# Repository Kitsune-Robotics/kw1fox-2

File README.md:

# kw1fox-2
Software and tools for the KW1FOX-2 radio station

## To clone

```
git clone --recurse-submodules https://github.com/Kitsune-Robotics/kw1fox-2
```

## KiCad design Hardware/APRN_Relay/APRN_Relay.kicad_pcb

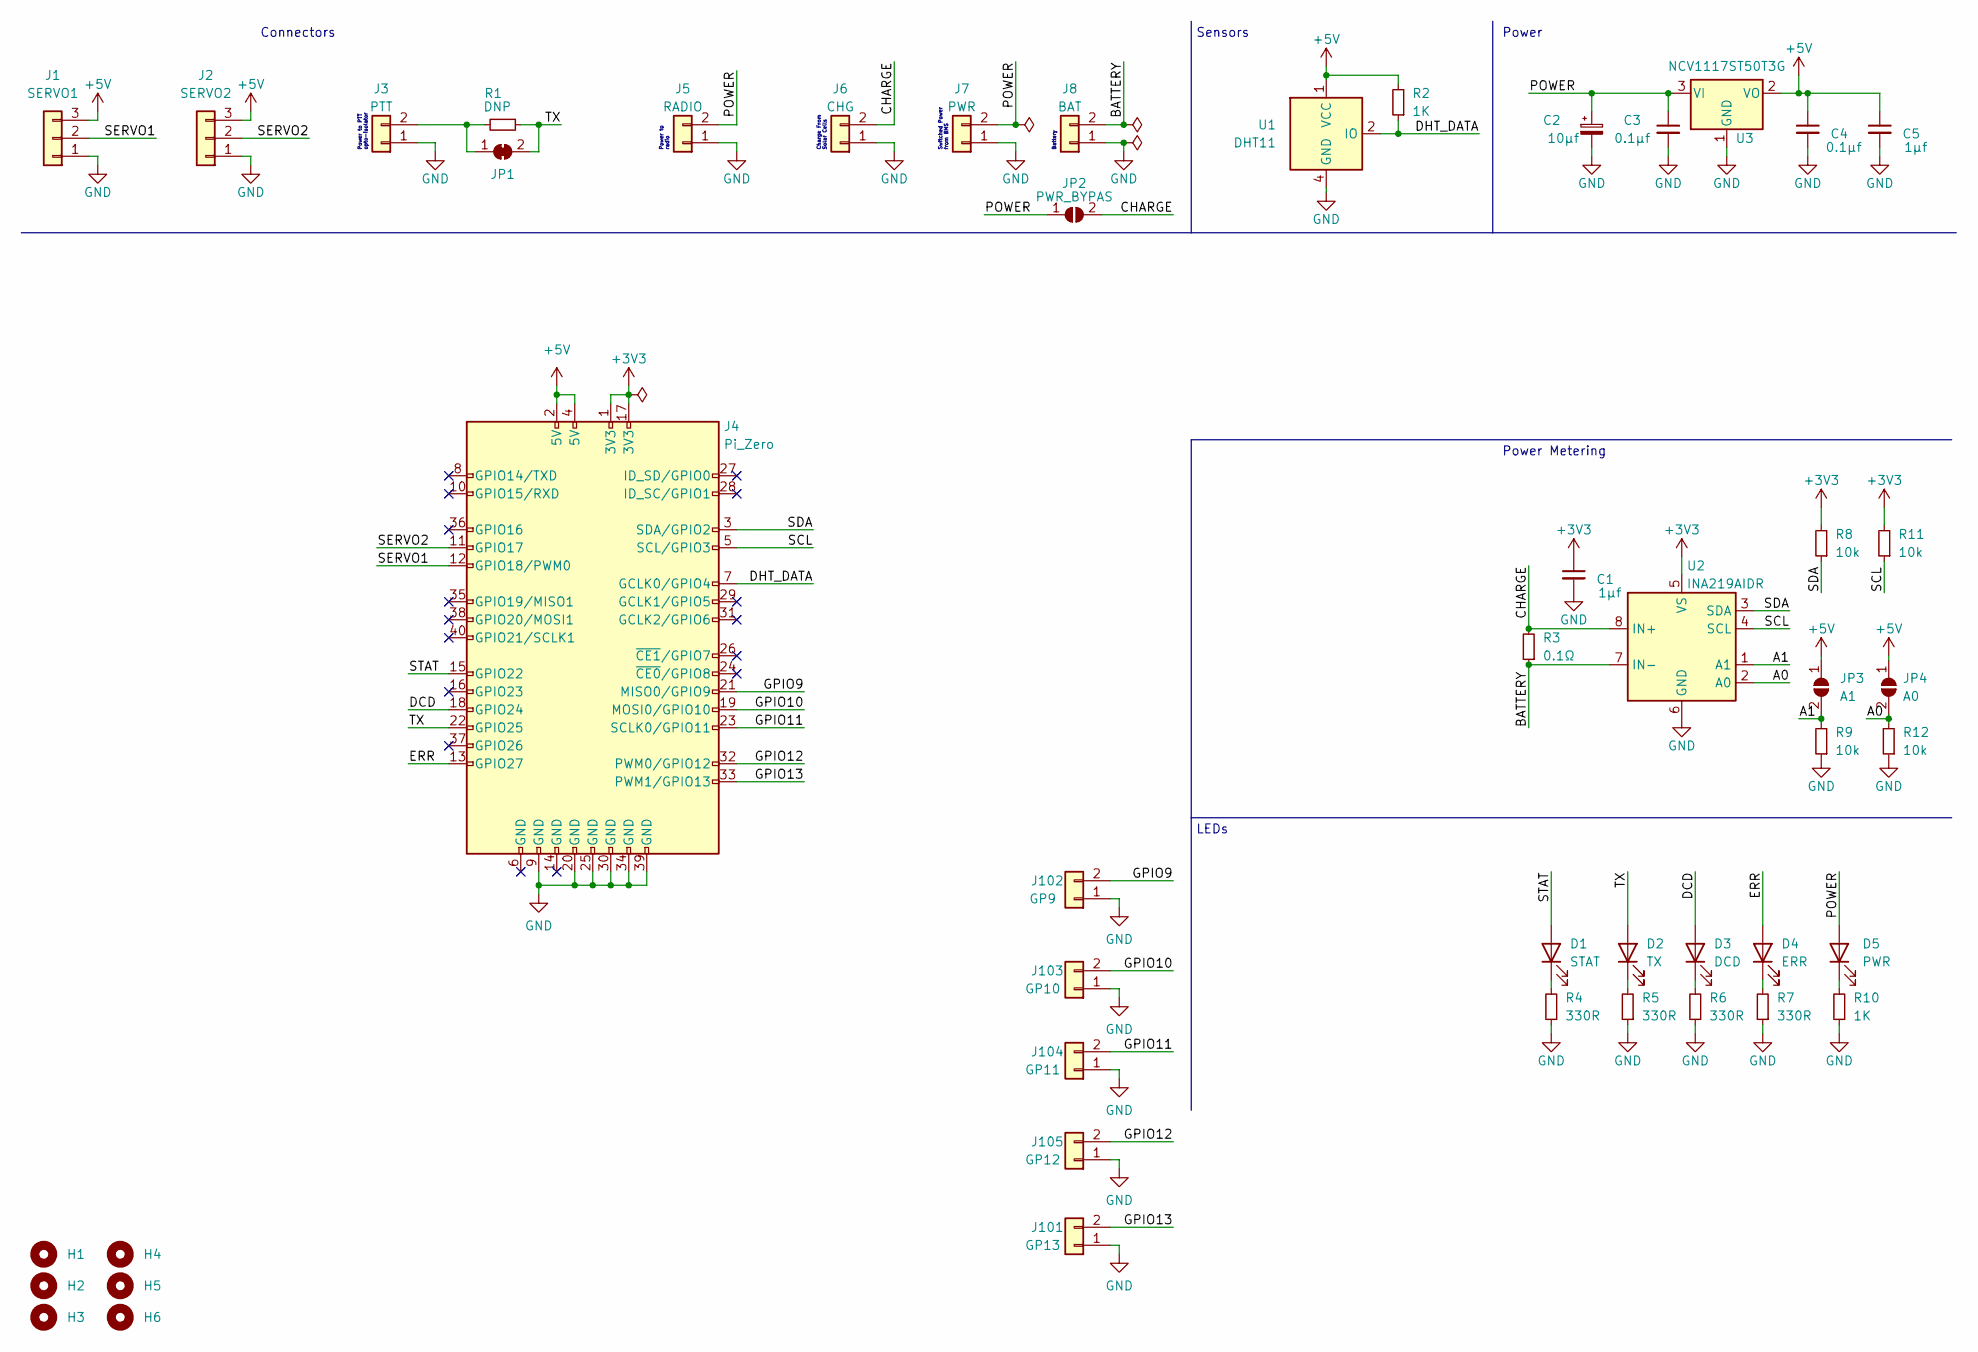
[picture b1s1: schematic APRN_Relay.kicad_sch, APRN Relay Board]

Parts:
C1, C5: 1μf; C_0805_2012Metric
C2: 10μf; CP_Elec_4x3
C3, C4: 0.1μf; C_0805_2012Metric
D1: STAT; LED_D3.0mm
D2: TX; LED_D3.0mm
D3: DCD; LED_D3.0mm
D4: ERR; LED_D3.0mm
D5: PWR; LED_D3.0mm
H1, H2, H3, H4, H5, H6: PiMountingHole; MountingHole_2.7mm
J1: SERVO1; JST_EH_S3B-EH_1x03_P2.50mm_Horizontal
J2: SERVO2; JST_EH_S3B-EH_1x03_P2.50mm_Horizontal
J3: PTT; JST_EH_S2B-EH_1x02_P2.50mm_Horizontal
J4: Pi_Zero; PinHeader_2x20_P2.54mm_Vertical
J5: RADIO; JST_EH_S2B-EH_1x02_P2.50mm_Horizontal
J6: CHG; JST_EH_S2B-EH_1x02_P2.50mm_Horizontal
J7: PWR; JST_EH_S2B-EH_1x02_P2.50mm_Horizontal
J8: BAT; JST_EH_S2B-EH_1x02_P2.50mm_Horizontal
J101: GP13; JST_EH_S2B-EH_1x02_P2.50mm_Horizontal
J102: GP9; JST_EH_S2B-EH_1x02_P2.50mm_Horizontal
J103: GP10; JST_EH_S2B-EH_1x02_P2.50mm_Horizontal
J104: GP11; JST_EH_S2B-EH_1x02_P2.50mm_Horizontal
J105: GP12; JST_EH_S2B-EH_1x02_P2.50mm_Horizontal
JP1: SolderJumper_2_Bridged; SolderJumper-2_P1.3mm_Bridged_Pad1.0x1.5mm
JP2: PWR_BYPAS; SolderJumper-2_P1.3mm_Open_TrianglePad1.0x1.5mm
JP3: A1; SolderJumper-2_P1.3mm_Open_TrianglePad1.0x1.5mm
JP4: A0; SolderJumper-2_P1.3mm_Open_TrianglePad1.0x1.5mm
R1: DNP; R_0805_2012Metric
R2, R10: 1K; R_0805_2012Metric
R3: 0.1Ω; R_2512_6332Metric
R4, R5, R6, R7: 330R; R_0805_2012Metric
R8, R9, R11, R12: 10k; R_0805_2012Metric
U1: DHT11; Aosong_DHT11_5.5x12.0_P2.54mm
U2: INA219AIDR; SOIC-8_3.9x4.9mm_P1.27mm
U3: NCV1117ST50T3G; SOT-223

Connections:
+3V3: C1.1, J4.1 (3V3), J4.17 (3V3), R8.2, R11.2, U2.5 (VS)
+5V: C4.1, C5.1, J1.3, J2.3, J4.2 (5V), J4.4 (5V), JP3.1 (A), JP4.1 (A), R2.2, U1.1 (VCC), U3.2 (VO)
/A0: JP4.2 (B), R12.2, U2.2 (A0)
/A1: JP3.2 (B), R9.2, U2.1 (A1)
/BATTERY: J8.2, R3.1, U2.7 (IN-)
/CHARGE: J6.2, JP2.2 (B), R3.2, U2.8 (IN+)
/DCD: D3.2 (A), J4.18 (GPIO24)
/DHT_DATA: J4.7 (GCLK0/GPIO4), R2.1, U1.2 (IO)
/ERR: D4.2 (A), J4.13 (GPIO27)
/GPIO9: J4.21 (MISO0/GPIO9), J102.2
/GPIO10: J4.19 (MOSI0/GPIO10), J103.2
/GPIO11: J4.23 (SCLK0/GPIO11), J104.2
/GPIO12: J4.32 (PWM0/GPIO12), J105.2
/GPIO13: J4.33 (PWM1/GPIO13), J101.2
/POWER: C2.1, C3.1, D5.2 (A), J5.2, J7.2, JP2.1 (A), U3.3 (VI)
/SCL: J4.5 (SCL/GPIO3), R11.1, U2.4 (SCL)
/SDA: J4.3 (SDA/GPIO2), R8.1, U2.3 (SDA)
/SERVO1: J1.2, J4.12 (GPIO18/PWM0)
/SERVO2: J2.2, J4.11 (GPIO17)
/STAT: D1.2 (A), J4.15 (GPIO22)
/TX: D2.2 (A), J4.22 (GPIO25), JP1.2 (B), R1.1
GND: C1.2, C2.2, C3.2, C4.2, C5.2, J1.1, J2.1, J3.1, J4.9 (GND), J4.20 (GND), J4.25 (GND), J4.30 (GND), J4.34 (GND), J4.39 (GND), J5.1, J6.1, J7.1, J8.1, J101.1, J102.1, J103.1, J104.1, J105.1, R4.1, R5.1, R6.1, R7.1, R9.1, R10.1, R12.1, U1.4 (GND), U2.6 (GND), U3.1 (GND)
unnamed: D1.1 (K), R4.2
unnamed: D2.1 (K), R5.2
unnamed: D3.1 (K), R6.2
unnamed: D4.1 (K), R7.2
unnamed: D5.1 (K), R10.2
unnamed: J3.2, JP1.1 (A), R1.2

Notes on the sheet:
Power to radio
Connectors
Battery
Sensors
Switched Power from BMS
Power Metering
Power to PTT opto-isolator
LEDs
Power
Charge From Solar Cells

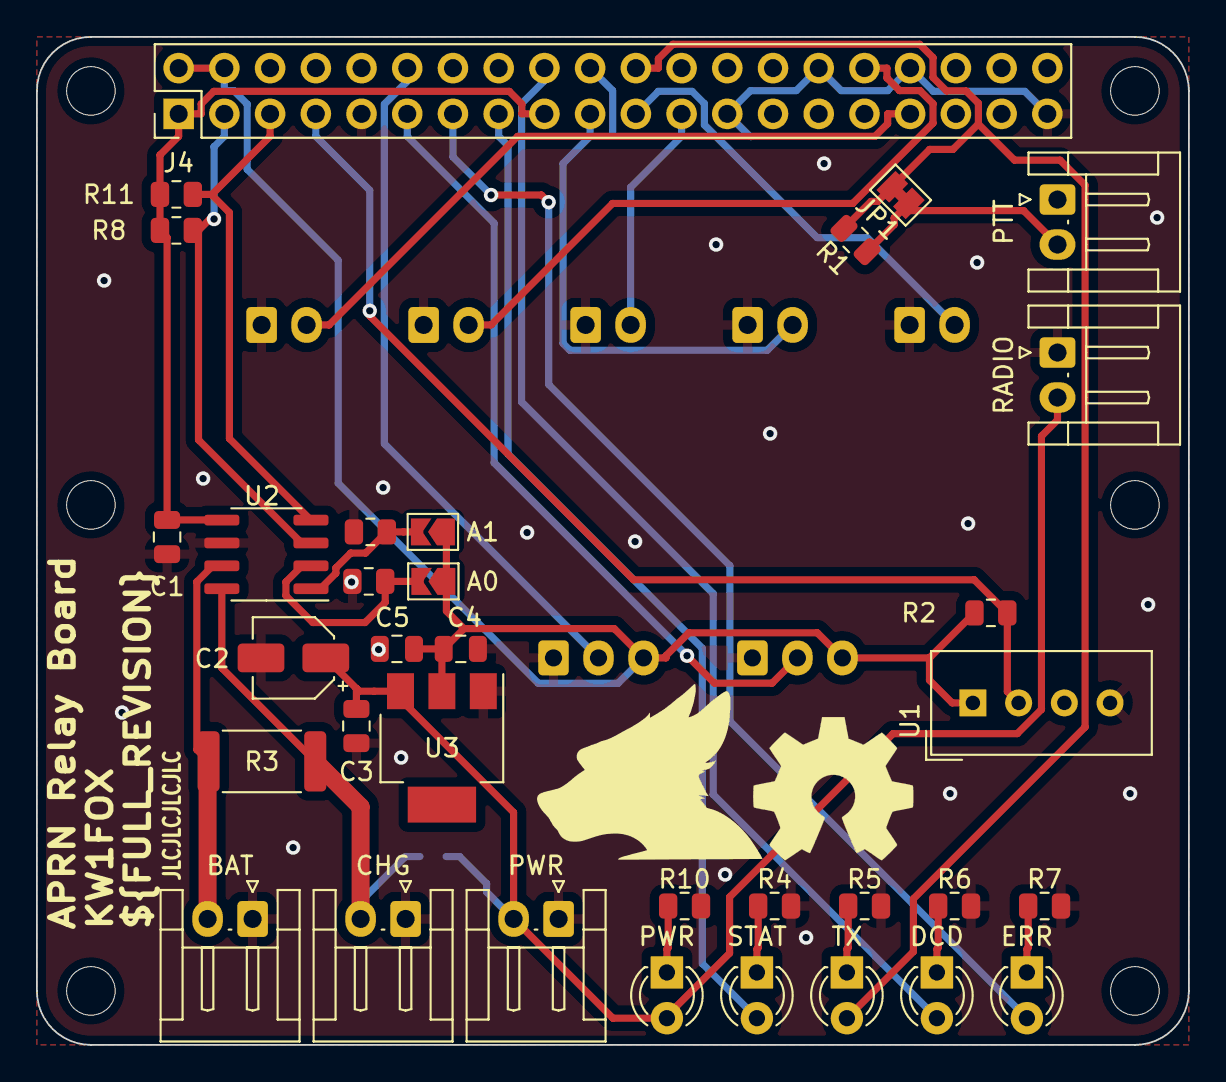
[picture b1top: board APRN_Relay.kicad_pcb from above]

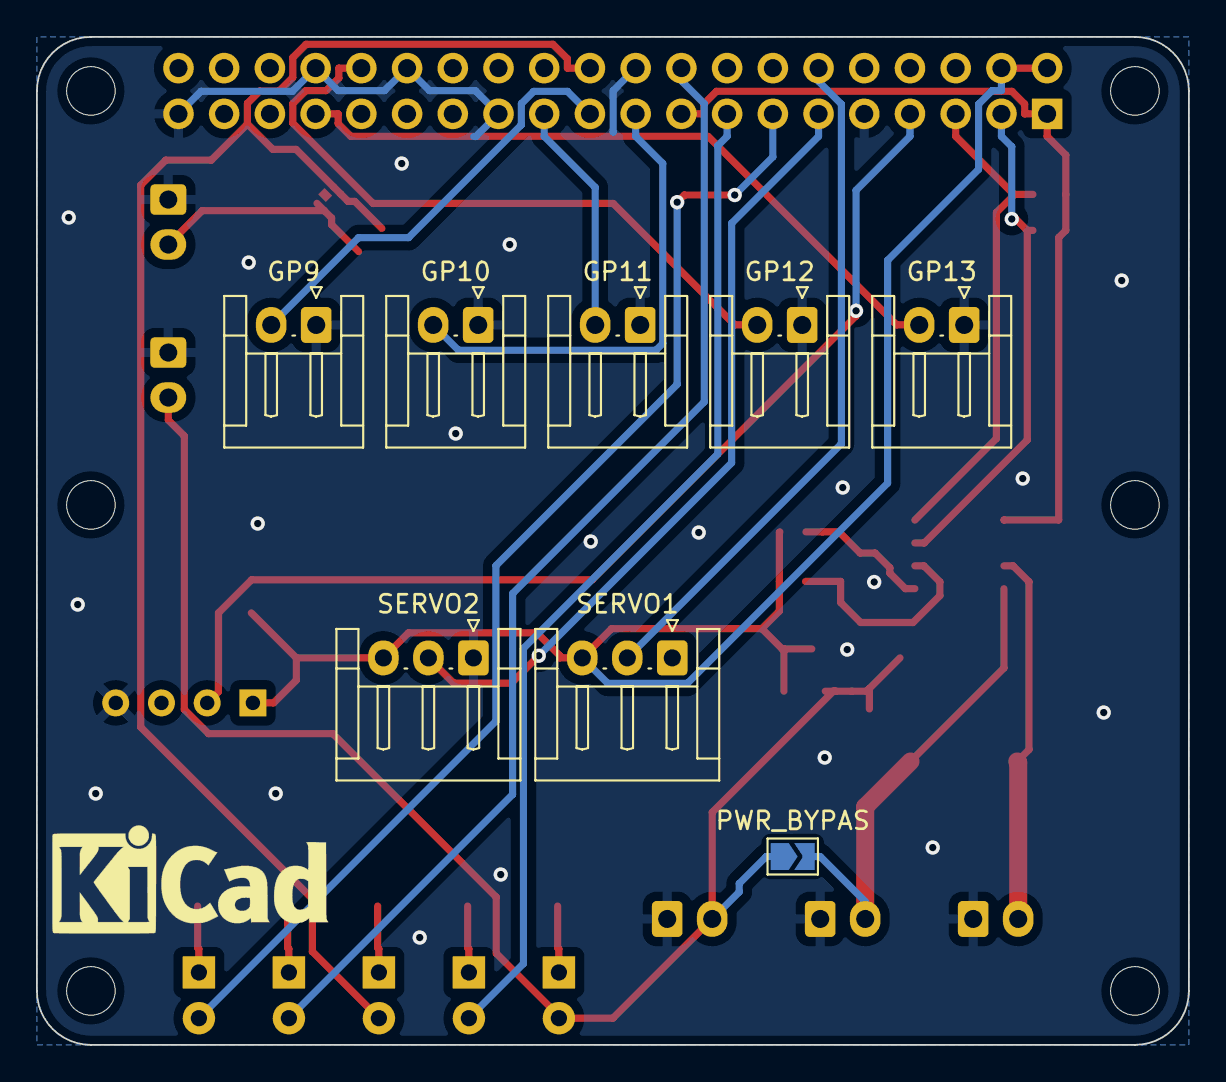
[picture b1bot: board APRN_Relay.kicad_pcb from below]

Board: 2 copper layers, 64.0 x 56.0 mm, 51 parts (9 on the bottom side), 28 nets.

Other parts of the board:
KICADLOGO: KiCad-Logo_6mm_SilkScreen
KTSNLOGO: LOGO; KITSUNE_LOGO
OSHWLOGO: OSHW-Symbol_8.9x8mm_SilkScreen

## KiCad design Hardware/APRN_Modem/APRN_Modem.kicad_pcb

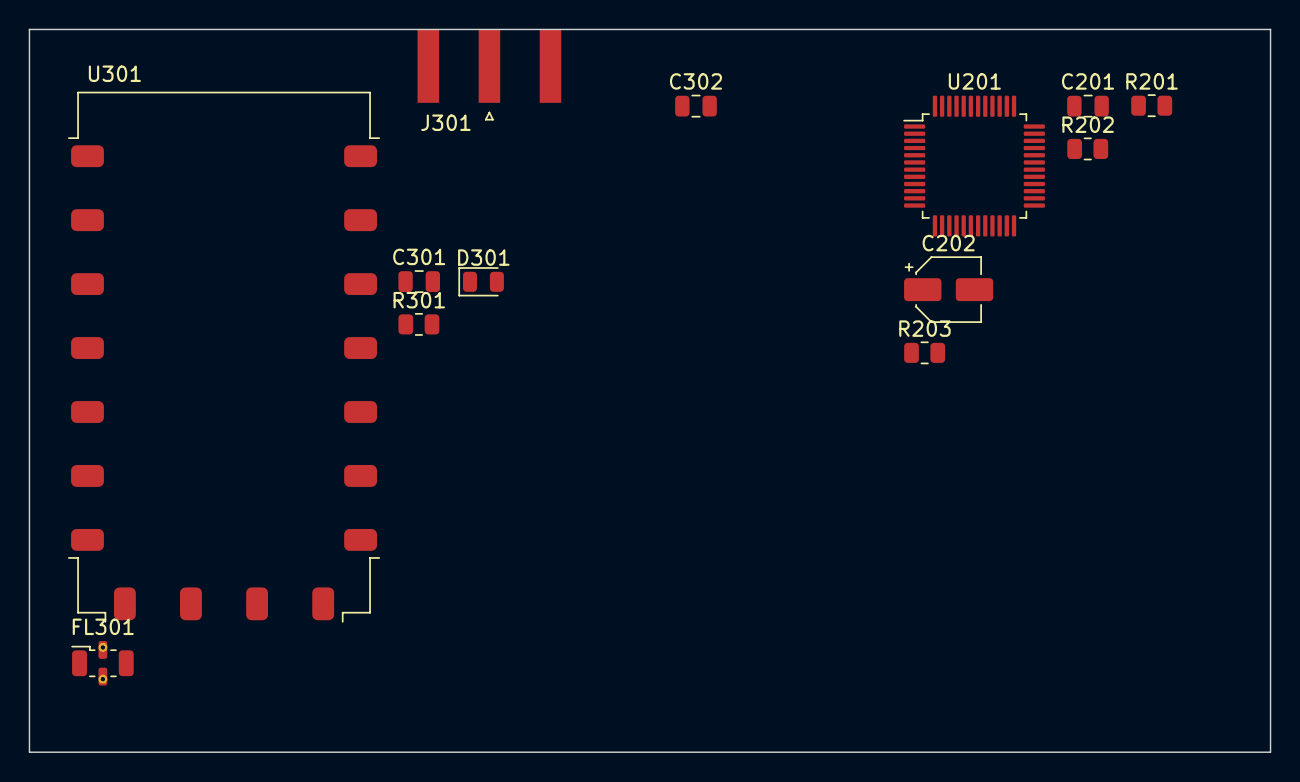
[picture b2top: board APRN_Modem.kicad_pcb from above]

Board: 2 copper layers, 86.4 x 50.3 mm, 13 parts (0 on the bottom side), 13 nets, no tracks yet.

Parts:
C201: 1uF; C_0805_2012Metric
C202: 10uf; CP_Elec_4x3
C301: 100pF; C_0805_2012Metric
C302: 4.7uF; C_0805_2012Metric
D301: RX; LED_0805_2012Metric
FL301: LFCN-490; Filter_Mini-Circuits_FV1206
J301: Conn_Coaxial; SMA_Amphenol_132289_EdgeMount
R201, R202, R203: 100K; R_0805_2012Metric
R301: 2K2; R_0805_2012Metric
U201: VS1003; LQFP-48_7x7mm_P0.5mm
U301: DRA818V

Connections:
+4V: C301.2, C302.2, U301.8 (VBAT)
/DRA818/SQ: D301.1 (K), U301.1 (SQ)
/VS1003/AVDD: U201.38 (AVDD0), U201.43 (AVDD1), U201.45 (AVDD2)
/VS1003/CVDD: U201.5 (CVDD0), U201.7 (CVDD1), U201.24 (CVDD2), U201.31 (CVDD3)
/VS1003/IOVDD: R203.1, U201.6 (IOVDD0), U201.14 (IOVDD1), U201.19 (IOVDD2), U201.32 (TEST)
/VS1003/~xRESET: R201.1, U201.3 (~xRESET)
GND: C201.1, C301.1, C302.1, FL301.2 (GND), FL301.4 (GND), J301.2 (Ext), R201.2, R202.2, U201.4 (DGND0), U201.16 (DGND1), U201.20 (DGND2), U201.21 (DGND3), U201.22 (DGND4), U201.37 (AGND0), U201.40 (AGND1), U201.41 (AGND2), U201.47 (AGND3), U301.9 (GND), U301.10 (GND)
unnamed: C201.2, U201.44 (RCAP)
unnamed: D301.2 (A), R301.2
unnamed: FL301.1 (IN), U301.12 (ANT)
unnamed: FL301.3 (OUT), J301.1 (In)
unnamed: R202.1, U201.33 (GPIO0)
unnamed: R203.2, U201.26 (RXD)

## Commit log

2022-04-12 import from kw1fox-2/software
2022-07-09 Inital new firmware
2022-07-09 Add firmware
2022-07-09 Lots of compilation errors
2022-07-09 Remove dupe
2022-07-27 Where i left off
2022-07-30 This does break the firmware but a fix is on the way
2022-07-30 New and improved KW1FOX-2 Hardware
2022-07-30 Stage all
2022-07-30 Cleanup DRA footprint
2022-07-30 Even prettier
2022-07-30 Do hardware things
2022-08-01 Add some things for the vs1003
2022-08-01 Move everything
2022-08-01 Clean the rest
2022-08-01 Last touchups
2022-08-03 Bump libs and stuff
2022-08-16 This builds a binary
2022-08-16 Still builds a binary
2022-08-31 Switch to mbed from picotool
2022-09-01 Switch back to picotool, and setup SDFS
2022-11-21 Layout hardware
2022-11-21 Move stuff around
2022-11-21 And thats how its done
2022-11-22 Inital kicad layout
2022-11-22 Boop
2022-11-22 Easier than fixing it
2022-11-22 Plz fix?
2022-11-22 This is good to go
2022-11-22 fixup! This is good to go
2022-11-22 Add text to the front (and ID for JLCPCB)
2022-11-22 Add pi 3d model
2022-11-23 Clean the last bits and prep for a tidy final review series, merge into 1.0 when done
2022-11-23 Add power flag to other side of load resistor
2022-11-23 make shunt resistor value more clear
2022-11-23 INA219 and I2C lines now driven by 3.3v instead of 5.0v
2022-11-24 Implement changes from dad
    Co-Authored By: ka2qfx
2022-11-24 Include last changes from dad, thanks!
2022-11-24 Also include static render
2022-11-24 Remove power flag from input of current sensor
2022-11-26 Add test
2022-11-27 Add things
2022-11-27 Add repaired kiss tx
2022-11-28 Add kicad logo to back
2022-12-02 Add PTT DNP
2022-12-14 Small setting in config.kibot.yaml causes board defs not to be printed on silkscreen
    Really annoyed i missed this but its too late now :c
2022-12-19 bump with new plugs on the back
2022-12-21 Inital stencil holder design
2022-12-22 This stencil fits pretty well
2022-12-22 Hide this one thing
2022-12-29 Add 3d models
2022-12-29 Broken but a good starting point
